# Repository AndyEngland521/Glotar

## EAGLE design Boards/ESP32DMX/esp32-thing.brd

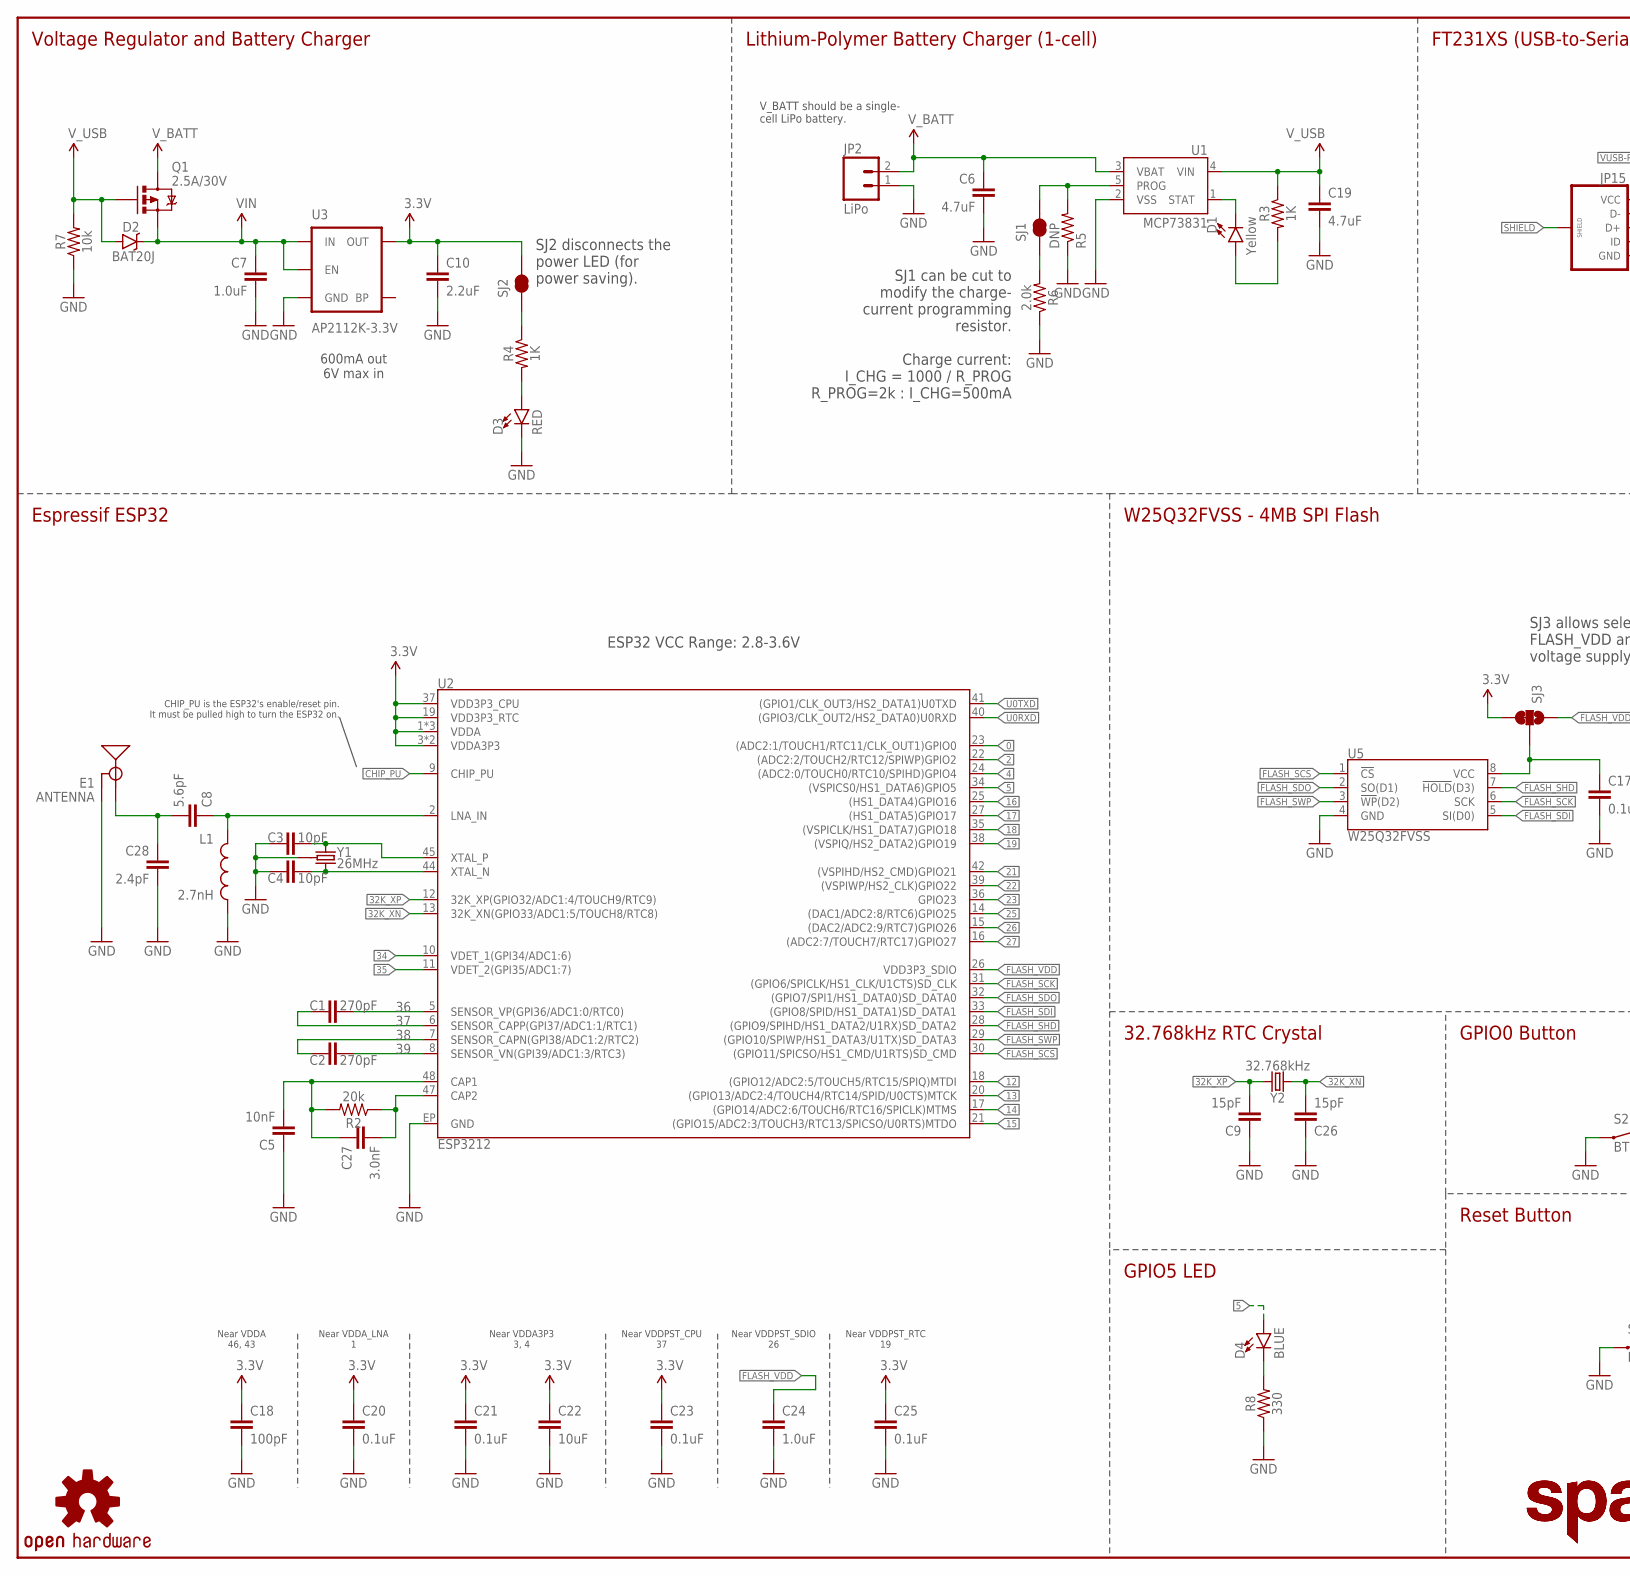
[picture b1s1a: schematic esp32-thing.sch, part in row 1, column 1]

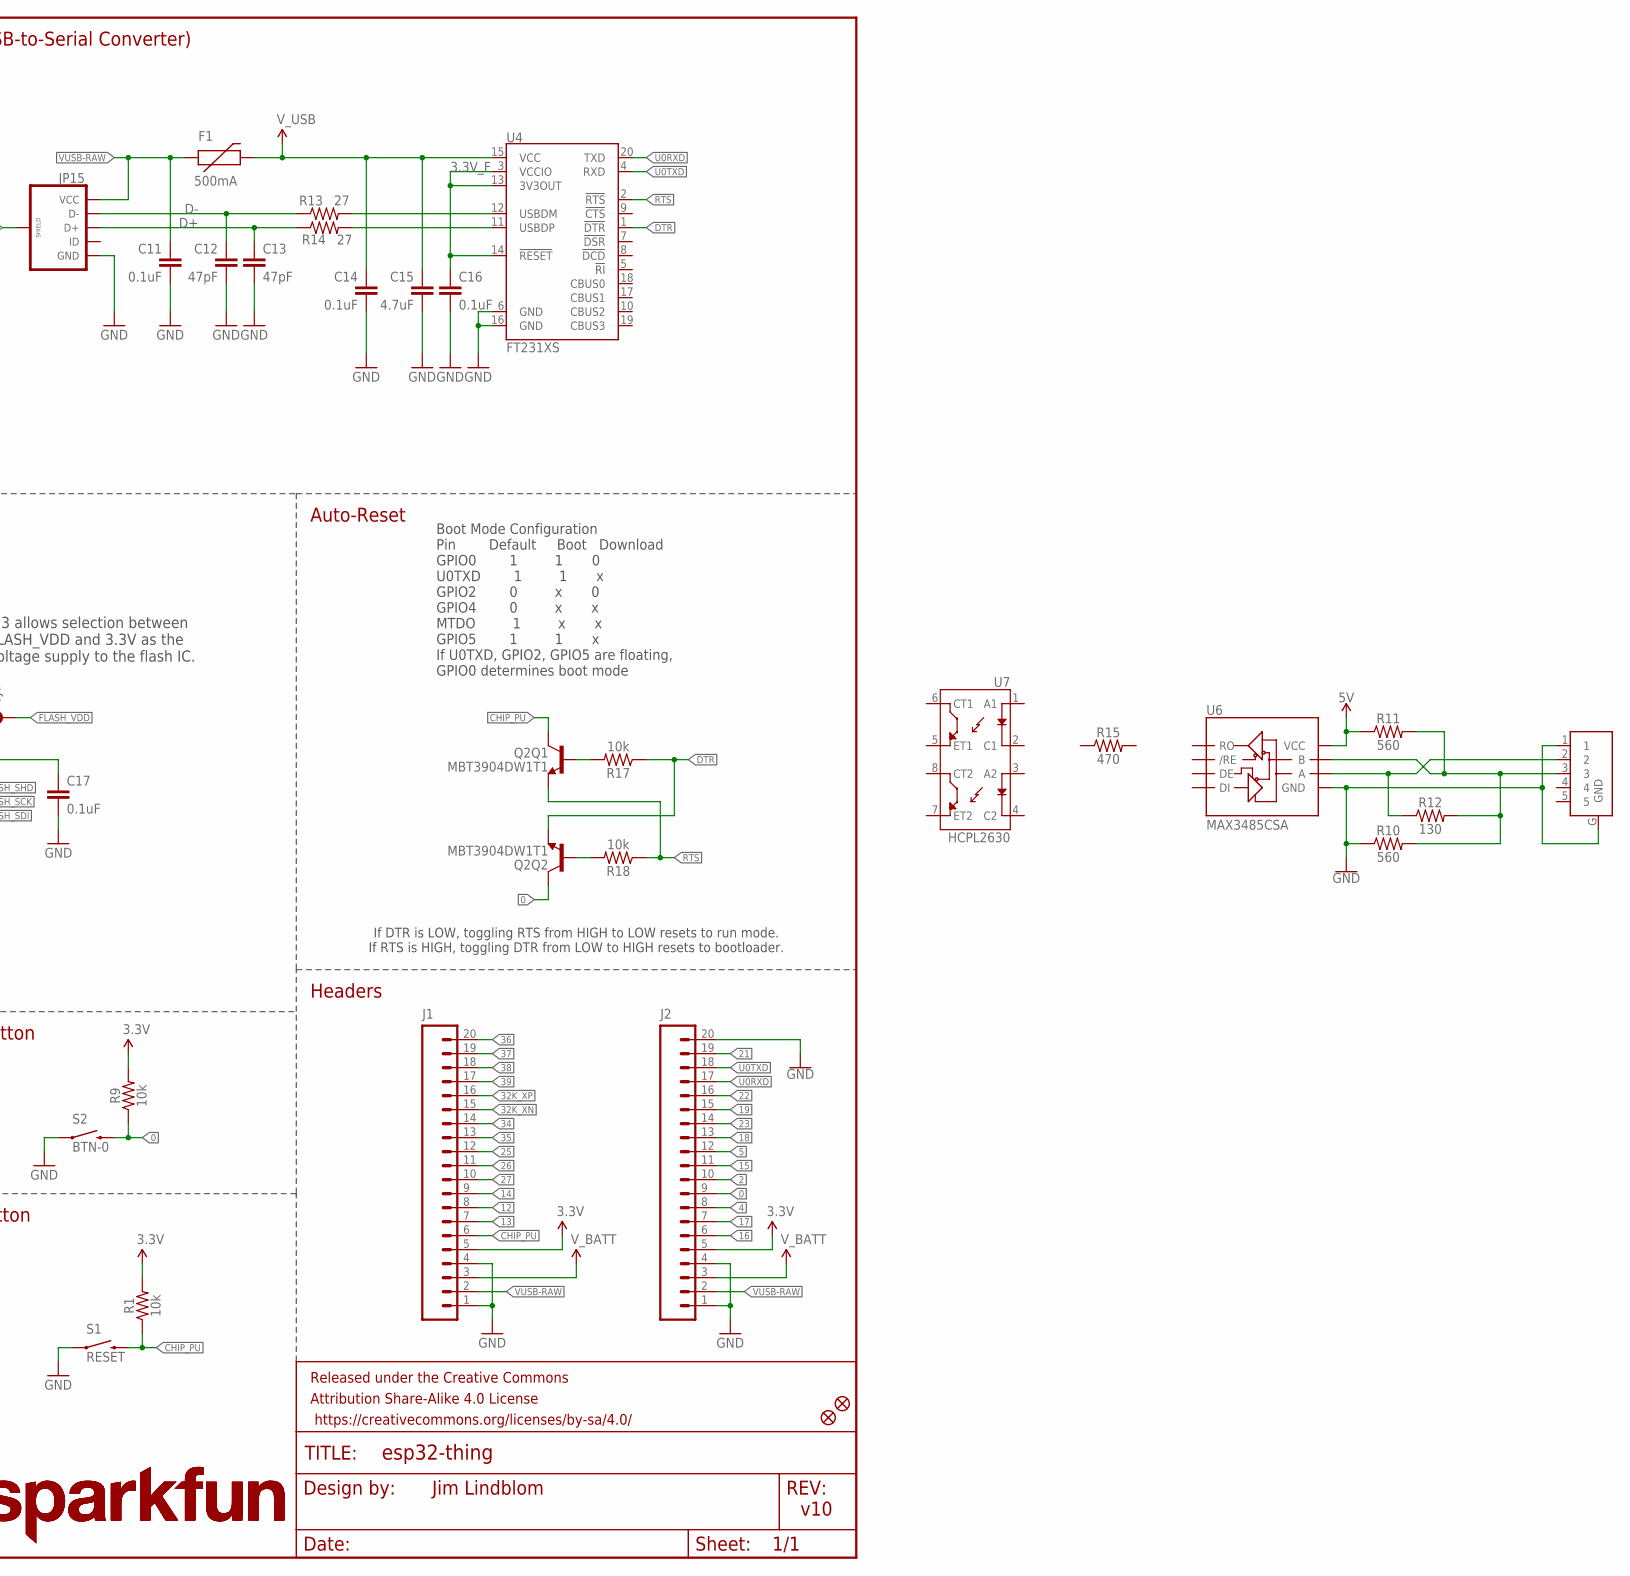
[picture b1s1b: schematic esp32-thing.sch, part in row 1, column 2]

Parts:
C1, C2: 270pF; 0603
C3, C4: 10pF; 0603
C5: 10nF; 0603
C6, C19: 4.7uF; 0603
C7: 1.0uF; 0805
C8: 5.6pF; 0603
C9, C26: 15pF; 0603
C10: 2.2uF; 0603
C11, C14, C16, C17, C20, C21, C23, C25: 0.1uF; 0603
C12, C13: 47pF; 0603
C15: 4.7uF; 0603-CAP
C18: 100pF; 0603
C22: 10uF; 0603
C24: 1.0uF; 0603
C27: 3.0nF; 0603
C28: 2.4pF; 0603
D1: Yellow; LED-0603
D2: BAT20J; SOD-323
D3: RED; LED-0603
D4: BLUE; LED-0603
E1: ANTENNA; TRACE_ANTENNA_2.4GHZ_25.7MM_TUNED
F1: 500mA; PTC-1206
FD1, FD2: FIDUCIALUFIDUCIAL; MICRO-FIDUCIAL
FRAME1: FRAME-LEDGER; CREATIVE_COMMONS
J1, J2: M20NOSILK; 1X20_NOSILK
JP2: LiPo; JST-2-PTH
JP15: USB_MICROB_PLUGCONN-11752; USB-B-MICRO-SMD_V03
L1: 2.7nH; 0603
LOGO1, LOGO3: SFE_LOGO_NAME.2_INCH; SFE_LOGO_NAME_.2
LOGO2: OSHW-LOGOMINI; OSHW-LOGO-MINI
Q1: 2.5A/30V; SOT23-3
Q2: MBT3904DW1T1; SC70-6
R1, R7, R9, R17, R18: 10k; 0603
R2: 20k; 0603
R3, R4: 1K; 0603
R5: DNP; 1/6W-RES
R6: 2.0k; 0603
R8: 330; 0603
R10, R11: 560; 0402
R12: 130; 0603
R13, R14: 27; 0603
R15: 470; 0603
S1: RESET; TACTILE_SWITCH_SMD_4.6X2.8MM
S2: BTN-0; TACTILE_SWITCH_SMD_4.6X2.8MM
SJ1, SJ2: JUMPER-PAD-2-NC_BY_TRACE; PAD-JUMPER-2-NC_BY_TRACE_YES_SILK
SJ3: JUMPER-PAD-3-2OF3_NC_BY_TRACE_SMALL; PAD-JUMPER-3-2OF3_NC_BY_TRACE_YES_SILK_FULL_BOX
U1: MCP73831; SOT23-5
U2: ESP3212; QFN48-0.4MM
U3: AP2112K-3.3V; SOT23-5
U4: FT231XS; SSOP20_L
U5: W25Q32FVSS; SOIC-8
U6: MAX3485CSA; SO08
U7: HCPL2630; SO08
U$1: XLR-5
Y1: 26MHz; CRYSTAL-SMD-3.2X2.5
Y2: 32.768kHz; CRYSTAL-SMD-3.2X1.5MM

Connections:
0: J2.9, Q2.6 (C), R9.1, S2.3 (2), S2.4 (2), U2.23 ((ADC2:1/TOUCH1/RTC11/CLK_OUT1)GPIO0)
2: J2.10, U2.22 ((ADC2:2/TOUCH2/RTC12/SPIWP)GPIO2)
3.3V: C10.1, C18.1, C20.1, C21.1, C22.1, C23.1, C25.1, J1.5, J2.5, R1.2, R9.2, SJ2.2, SJ3.3, U2.1 (VDDA), U2.3 (VDDA3P3), U2.4 (VDDA3P3), U2.19 (VDD3P3_RTC), U2.37 (VDD3P3_CPU), U2.43 (VDDA), U2.46 (VDDA), U3.5 (OUT)
3.3V_F: C16.1, U4.3 (VCCIO), U4.13 (3V3OUT), U4.14 (!RESET)
4: J2.8, U2.24 ((ADC2:0/TOUCH0/RTC10/SPIHD)GPIO4)
5: D4.A, J2.12, U2.34 ((VSPICS0/HS1_DATA6)GPIO5)
5V: R11.1, U6.8 (VCC)
12: J1.8, U2.18 ((GPIO12/ADC2:5/TOUCH5/RTC15/SPIQ)MTDI)
13: J1.7, U2.20 ((GPIO13/ADC2:4/TOUCH4/RTC14/SPID/U0CTS)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)
14: J1.9, U2.17 ((GPIO14/ADC2:6/TOUCH6/RTC16/SPICLK)MTMS)
15: J2.11, U2.21 ((GPIO15/ADC2:3/TOUCH3/RTC13/SPICSO/U0RT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)
16: J2.6, U2.25 ((HS1_DATA4)GPIO16)
17: J2.7, U2.27 ((HS1_DATA5)GPIO17)
18: J2.13, U2.35 ((VSPICLK/HS1_DATA7)GPIO18)
19: J2.15, U2.38 ((VSPIQ/HS2_DATA2)GPIO19)
21: J2.19, U2.42 ((VSPIHD/HS2_CMD)GPIO21)
22: J2.16, U2.39 ((VSPIWP/HS2_CLK)GPIO22)
23: J2.14, U2.36 (GPIO23)
25: J1.12, U2.14 ((DAC1/ADC2:8/RTC6)GPIO25)
26: J1.11, U2.15 ((DAC2/ADC2:9/RTC7)GPIO26)
27: J1.10, U2.16 ((ADC2:7/TOUCH7/RTC17)GPIO27)
32K_XN: C26.2, J1.15, U2.13 (32K_XN(GPIO33/ADC1:5/TOUCH8/RTC8)), Y2.P$2 (2)
32K_XP: C9.2, J1.16, U2.12 (32K_XP(GPIO32/ADC1:4/TOUCH9/RTC9)), Y2.P$1 (1)
34: J1.14, U2.10 (VDET_1(GPI34/ADC1:6))
35: J1.13, U2.11 (VDET_2(GPI35/ADC1:7))
36: C1.2, J1.20, U2.5 (SENSOR_VP(GPI36/ADC1:0/RTC0))
37: C1.1, J1.19, U2.6 (SENSOR_CAPP(GPI37/ADC1:1/RTC1))
38: C2.1, J1.18, U2.7 (SENSOR_CAPN(GPI38/ADC1:2/RTC2))
39: C2.2, J1.17, U2.8 (SENSOR_VN(GPI39/ADC1:3/RTC3))
CAP_10N: C5.2, C27.1, R2.2, U2.48 (CAP1)
CHIP_PU: J1.6, Q2.3 (C), R1.1, S1.3 (2), S1.4 (2), U2.9 (CHIP_PU)
D+: C13.1, JP15.D+, R14.1
D-: C12.1, JP15.D-, R13.1
DTR: Q2.1 (E), R17.1, U4.1 (!DTR)
FLASH_SCK: U2.31 ((GPIO6/SPICLK/HS1_CLK/U1CTS)SD_CLK), U5.6 (SCK)
FLASH_SCS: U2.30 ((GPIO11/SPICSO/HS1_CMD/U1RTS)SD_CMD), U5.1 (!CS!)
FLASH_SDI: U2.33 ((GPIO8/SPID/HS1_DATA1)SD_DATA1), U5.5 (SI(D0))
FLASH_SDO: U2.32 ((GPIO7/SPI1/HS1_DATA0)SD_DATA0), U5.2 (SO(D1))
FLASH_SHD: U2.28 ((GPIO9/SPIHD/HS1_DATA2/U1RX)SD_DATA2), U5.7 (!HOLD!(D3))
FLASH_SWP: U2.29 ((GPIO10/SPIWP/HS1_DATA3/U1TX)SD_DATA3), U5.3 (!WP!(D2))
FLASH_VDD: C24.1, SJ3.1, U2.26 (VDD3P3_SDIO)
GND: C3.1, C4.1, C5.1, C6.2, C7.2, C9.1, C10.2, C11.2, C12.2, C13.2, C14.2, C15.2, C16.2, C17.2, C18.2, C19.2, C20.2, C21.2, C22.2, C23.2, C24.2, C25.2, C26.1, C28.2, D3.C, E1.GND, E1.GND2 (GND), J1.1, J1.4, J2.1, J2.4, J2.20, JP2.1, JP15.GND, L1.2, R5.1, R6.1, R7.1, R8.1, R10.1, S1.1, S1.2 (1), S2.1, S2.2 (1), U1.2 (VSS), U2.EP (GND), U3.2 (GND), U4.6 (GND), U4.16 (GND), U5.4 (GND), U6.5 (GND), U$1.1, U$1.G (GND), Y1.2 (GND), Y1.4 (GND)
LNA_IN: C8.1, L1.1, U2.2 (LNA_IN)
unnamed: D4.C, R8.2
unnamed: D3.A, R4.2
unnamed: R4.1, SJ2.1
unnamed: C27.2, R2.1, U2.47 (CAP2)
unnamed: R13.2, U4.12 (USBDM)
unnamed: R14.2, U4.11 (USBDP)
unnamed: D1.C, U1.1 (STAT)
unnamed: Q2.5 (B), R17.2
unnamed: C17.1, SJ3.2, U5.8 (VCC)
unnamed: Q2.2 (B), R18.2
unnamed: C3.2, U2.45 (XTAL_P), Y1.1
unnamed: R5.2, SJ1.2, U1.5 (PROG)
unnamed: C4.2, U2.44 (XTAL_N), Y1.3 (2)
unnamed: R6.2, SJ1.1
unnamed: D1.A, R3.2
unnamed: R10.2, R11.2, R12.2, U6.7 (B), U$1.3
unnamed: R12.1, U6.6 (A), U$1.2
RTS: Q2.4 (E), R18.1, U4.2 (!RTS)
SHIELD: JP15.SHIELD1 (SHIELD), JP15.SHIELD2 (SHIELD), JP15.SHIELD3 (SHIELD)
TRACE_ANT: C8.2, C28.1, E1.ANT (SIGNAL)
U0RXD: J2.17, U2.40 ((GPIO3/CLK_OUT2/HS2_DATA0)U0RXD), U4.20 (TXD)
U0TXD: J2.18, U2.41 ((GPIO1/CLK_OUT3/HS2_DATA1)U0TXD), U4.4 (RXD)
VIN: C7.1, D2.C, Q1.2 (S), U3.1 (IN), U3.3 (EN)
VUSB-RAW: C11.1, F1.1, J1.2, J2.2, JP15.VBUS (VCC)
V_BATT: C6.1, J1.3, J2.3, JP2.2, Q1.3 (D), U1.3 (VBAT)
V_USB: C14.1, C15.1, C19.1, D2.A, F1.2, Q1.1 (G), R3.1, R7.2, U1.4 (VIN), U4.15 (VCC)

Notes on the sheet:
Boot Mode Configuration Pin Default Boot Download GPIO0 1 1 0 U0TXD 1 1 x GPIO2 0 x 0 GPIO4 0 x x MTDO 1 x x GPIO5 1 1 x If U0TXD, GPIO2, GPIO5 are floating, GPIO0 determines boot mode
FT231XS (USB-to-Serial Converter)
V_BATT should be a single- cell LiPo battery.
Charge current: I_CHG = 1000 / R_PROG R_PROG=2k : I_CHG=500mA
Voltage Regulator and Battery Charger
SJ1 can be cut to modify the charge- current programming resistor.
Lithium-Polymer Battery Charger (1-cell)
600mA out 6V max in
Auto-Reset
Near VDDA 46, 43
Near VDDA_LNA 1
Near VDDA3P3 3, 4
Near VDDPST_CPU 37
Near VDDPST_SDIO 26
Near VDDPST_RTC 19
Espressif ESP32
W25Q32FVSS - 4MB SPI Flash
32.768kHz RTC Crystal
GPIO0 Button
Reset Button
GPIO5 LED
Headers
v10
Jim Lindblom
ESP32 VCC Range: 2.8-3.6V
SJ3 allows selection between FLASH_VDD and 3.3V as the voltage supply to the flash IC.
SJ2 disconnects the power LED (for power saving).
If DTR is LOW, toggling RTS from HIGH to LOW resets to run mode. If RTS is HIGH, toggling DTR from LOW to HIGH resets to bootloader.
CHIP_PU is the ESP32's enable/reset pin. It must be pulled high to turn the ESP32 on.

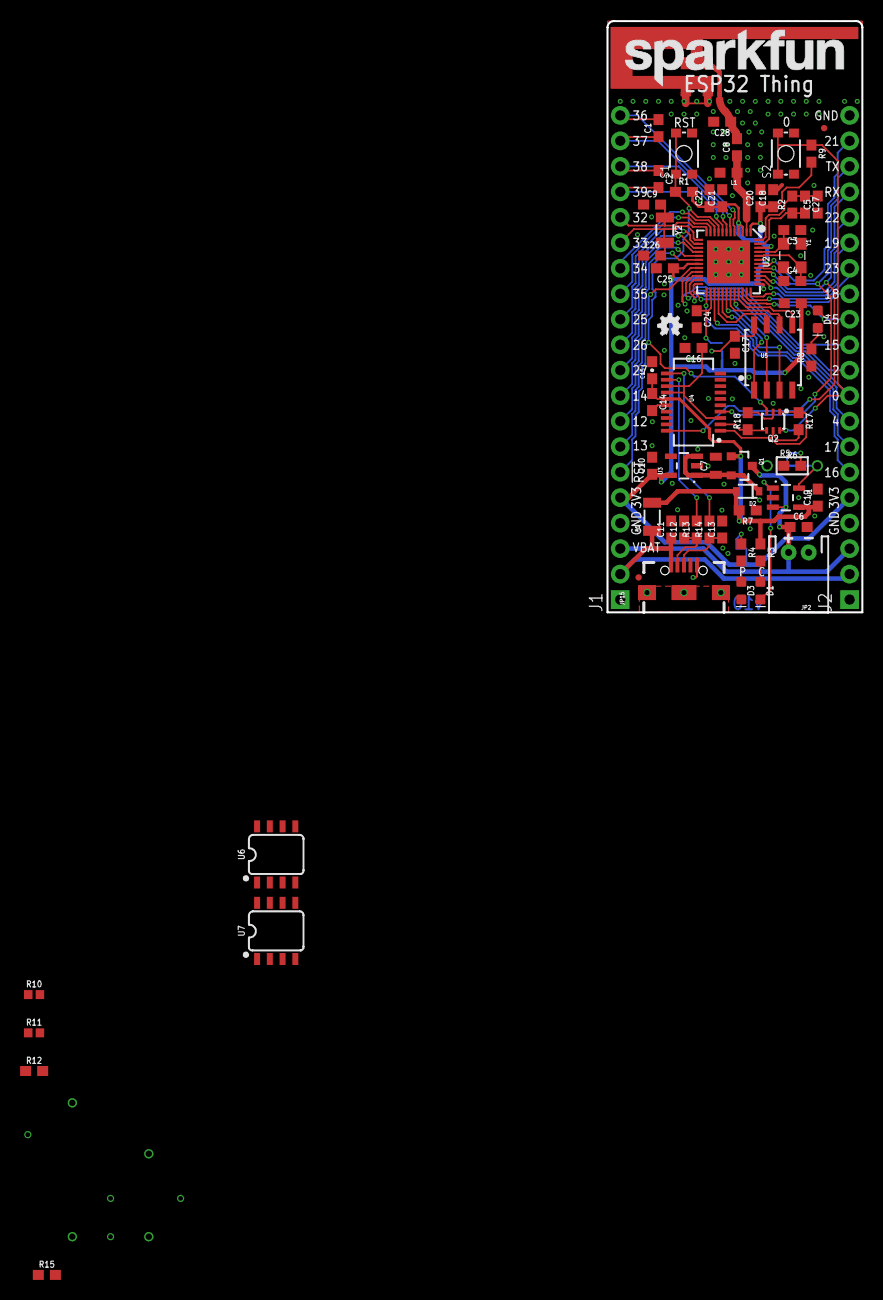
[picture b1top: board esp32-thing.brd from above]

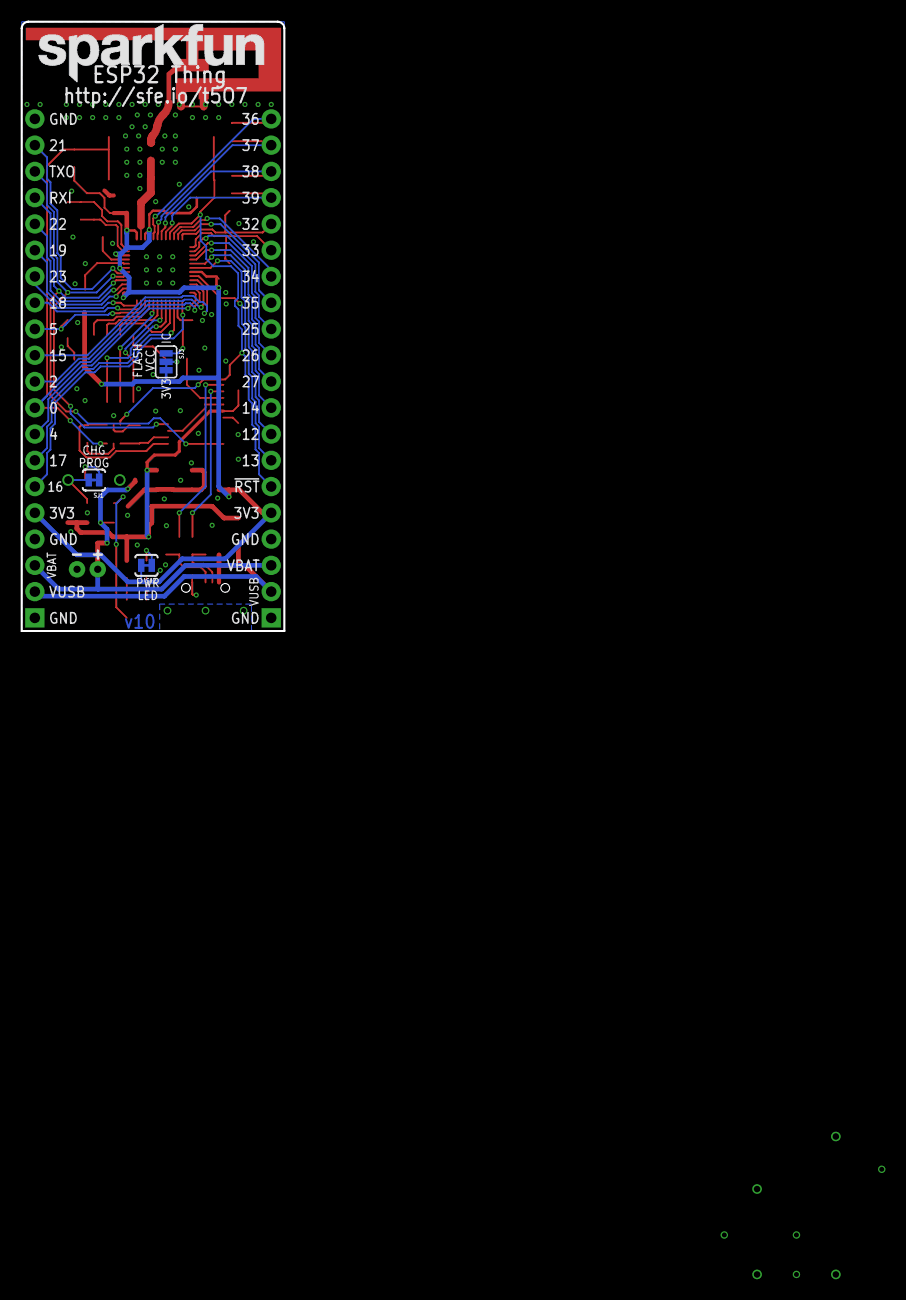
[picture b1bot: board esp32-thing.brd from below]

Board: 2 copper layers, 25.4 x 58.9 mm, 79 parts (4 on the bottom side), 69 nets.

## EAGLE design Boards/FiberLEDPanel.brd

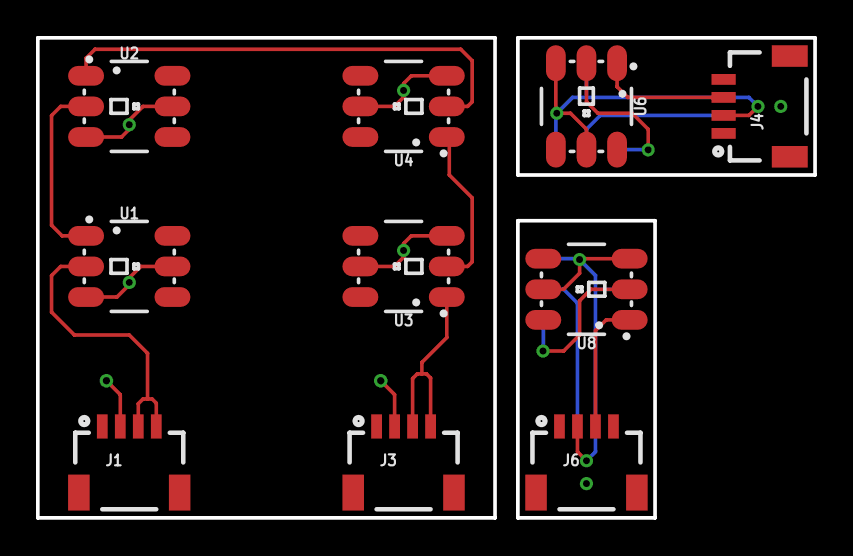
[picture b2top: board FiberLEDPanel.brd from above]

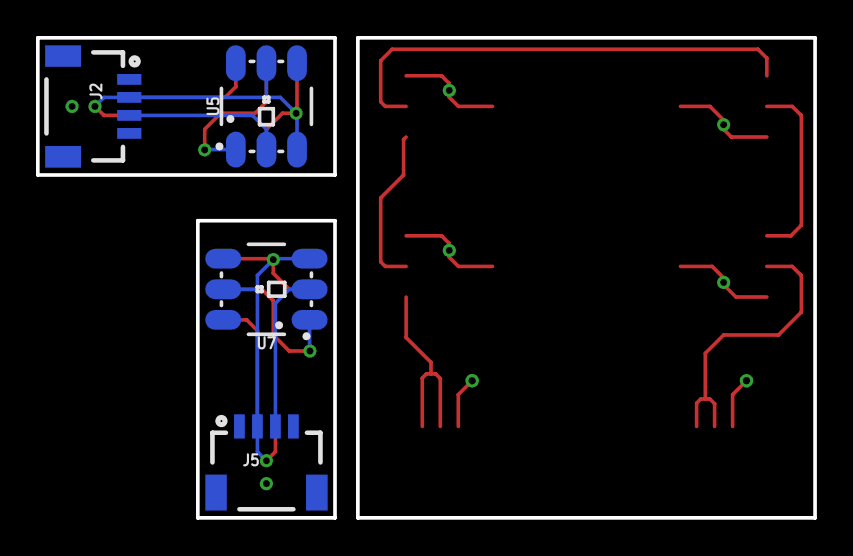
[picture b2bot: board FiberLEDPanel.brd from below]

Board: 2 copper layers, 43.2 x 26.7 mm, 16 parts (4 on the bottom side), 17 nets.

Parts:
FRAME1, FRAME2: FRAME-LETTER; CREATIVE_COMMONS
J1, J2, J3, J4, J5, J6: 1X04_1MM_RA
U1, U2, U3, U4, U5, U6, U7, U8: WS2812; LED-TRICOLOR-5050-IC

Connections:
5V: J1.2, J3.2, U1.3, U1.5, U2.3, U2.5, U3.3, U3.5, U4.3, U4.5
5V1: J2.2, J4.2, U5.3, U5.5, U6.3, U6.5
5V2: J5.2, J6.2, U7.3, U7.5, U8.3, U8.5
GND: J1.1, J3.1, U1.6, U2.6, U3.6, U4.6
GND1: J2.1, J4.1, U5.6, U6.6
GND2: J5.1, J6.1, U7.6, U8.6
unnamed: J1.3, J1.4, U1.2
unnamed: U3.2, U4.1
unnamed: U2.1, U4.2
unnamed: J3.3, J3.4, U3.1
unnamed: U1.1, U2.2
unnamed: U5.1, U6.2
unnamed: J2.3, U5.2
unnamed: J4.3, U6.1
unnamed: U7.1, U8.2
unnamed: J5.3, U7.2
unnamed: J6.3, U8.1

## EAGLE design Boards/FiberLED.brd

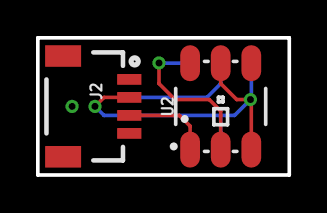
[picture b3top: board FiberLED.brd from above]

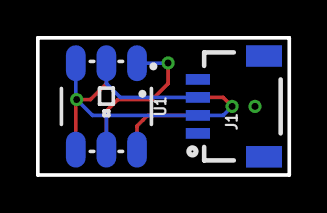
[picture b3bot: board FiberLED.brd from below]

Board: 2 copper layers, 14.0 x 7.6 mm, 5 parts (2 on the bottom side), 5 nets.

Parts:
FRAME1: FRAME-LETTER; CREATIVE_COMMONS
J1, J2: 1X04_1MM_RA
U1, U2: WS2812; LED-TRICOLOR-5050-IC

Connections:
5V: J1.2, J2.2, U1.3, U1.5, U2.3, U2.5
GND: J1.1, J2.1, U1.6, U2.6
unnamed: J1.3, U1.2
unnamed: J2.3, U2.1
unnamed: U1.1, U2.2

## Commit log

2018-07-09 adding led board
2018-07-10 Single Grip still needs work
2018-07-11 added and ordered LEDs
2018-07-11 Adding gcode
2018-07-17 Adding single grip
2018-07-24 adding mirrored fg
2018-07-25 updating test code
2018-07-26 Thinning the Mount
2018-07-26 adding board for ESP32DMX
2018-08-07 bringing mounting holes in slightly
2018-08-07 adding fg-single
2018-08-07 adding the multiples
2018-08-08 adding neck
2018-08-08 more gcode
2018-08-09 updating neck
2018-08-09 connecting fibergrip
2018-08-09 adding test gcode
2018-08-09 adding neck gcode
2018-08-09 adding fg_single
2018-08-09 finishing neck
2018-08-15 adding bens house code
2018-08-24 photoshoot
2018-09-10 starting combination of dmx and presets
2018-09-17 adding some artnew stuff
2018-09-19 adding artnet debug
2018-09-20 updating dmx to working version, 7fps
2018-09-28 its done
2018-09-28 adding maps

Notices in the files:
parts and their libraries:
SparkFun-Electromechanical: Licensing: Creative Commons ShareAlike 4.0 International - https://creativecommons.org/licenses/by-sa/4.0
SparkFun-Aesthetics: Released under the Creative Commons Attribution Share-Alike 4.0 License
SparkFun-Aesthetics: https://creativecommons.org/licenses/by-sa/4.0
